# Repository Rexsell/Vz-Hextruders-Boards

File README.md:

This project introduces convenient and useful PCBs designed for the [Vz-Hextrudort-Low](https://github.com/VzBoT3D/Vz-HextrudORT) and [Vz-Hextrudort-Plus](https://aliexpress.com/item/1005006121253410.html?shpMethod=CAINIAO_STANDARD&sku_id=12000036371654824&spm=a2g2w.stores.seller_list.3.317450c0yMkG1R)
Currently, there are no fully suitable toolboards for VzHextruders, as existing options require additional printed parts and are not 100% compatible with the [Vz-Printhead](https://github.com/VzBoT3D/Vz-Printhead-CNC)

# Prerequisites

Before installation, ensure you have a compatible [X-Endstop mount](https://www.printables.com/model/1297201-x-endstop-mount)
Also, use the correct hardware:
- M3x25 screw (for both extruders)
- M3x6 screw (Hextrudort-Low)
- M3x16 screw (Hextrudort-Plus)
- M3 standoffs (Length equal to your motor's height. You may also need a 0.5mm spacer for LDO motors.)
  
# Boards

## [VzHextrudortLow](https://github.com/Rexsell/Vz-Hextrudort-Boards/tree/main/VzHextrudortLow "VzHextrudortLow") and [VzHextrudortPlus](https://github.com/Rexsell/Vz-Hextrudort-Boards/tree/main/VzHextrudortPlus "VzHextrudortPlus")

They are simple commutation boards, they require Molex Microfit 2x10 as an input. Just direct connection, simple yet useful.

## [VzHextrudortPlusCan](https://github.com/Rexsell/Vz-Hextrudort-Boards/tree/main/VzHextrudortPlusCan "VzHextrudortPlusCan") and [VzHextrudortPlusUSB](https://github.com/Rexsell/Vz-Hextrudort-Boards/tree/main/VzHextrudortPlusUSB "VzHextrudortPlusUSB")
These are already CAN and USB boards respectively. USB version has several additional USB connectors for Beacon/Cartographer sensors and other devices. CAN board has only one CAN connector for external devices.

First of all, they are simpled version of toolboards. They were made as two-layer, singlesided PCBs in order to reduce cost and make them assemblable at home.
Secondly, CAN version I ordered and assembled two times, second one I corrected several mistakes. 

Features:
- Onboard NTC sensor
- TMC2209
- Connectors for external probes
- Connector for FilGuard sensor (Supports simple endstop)
- MAX31865 (Only for USB version curently)
- Solder jumper to turn off power LEDs
- RGB LED for motor backlight (Only for USB)
- Molex Microfit 3.0 for heater
- PFET protection from reversed polarity
- 2 Fans connectors

## WARNING!!!

**Before using this project, double-check the hotnd sensor connector schematic. I experienced unstable readings due to this configuration. The cause could be poorly chosen components, suboptimal routing, or a faulty schematic. The issue was completely resolved after connecting the same PT1000 sensor to a MAX31865 board. I used the BTT EBB36 schematic as a reference, but I don't recall exactly how I selected the components — I may have chosen incorrect ones.**

## [VzLowCan-Pro](https://github.com/Rexsell/Vz-Hextrudort-Boards/tree/main/VzLowCan-Pro "VzLowCan-Pro")

It shares the same features (and issues) as the [VzHextrudortPlusUSB](https://github.com/Rexsell/Vz-Hextrudort-Boards/tree/main/VzHextrudortPlusUSB "VzHextrudortPlusUSB"). However, this version is adapted for the -Low model and includes several additional features, such as an extended configuration for the MAX31865 and a connector for a probe like the BL-Touch. It also has a jumper for fan voltage selection. The design is not yet finalized, but I believe more experienced engineers will be able to complete it.

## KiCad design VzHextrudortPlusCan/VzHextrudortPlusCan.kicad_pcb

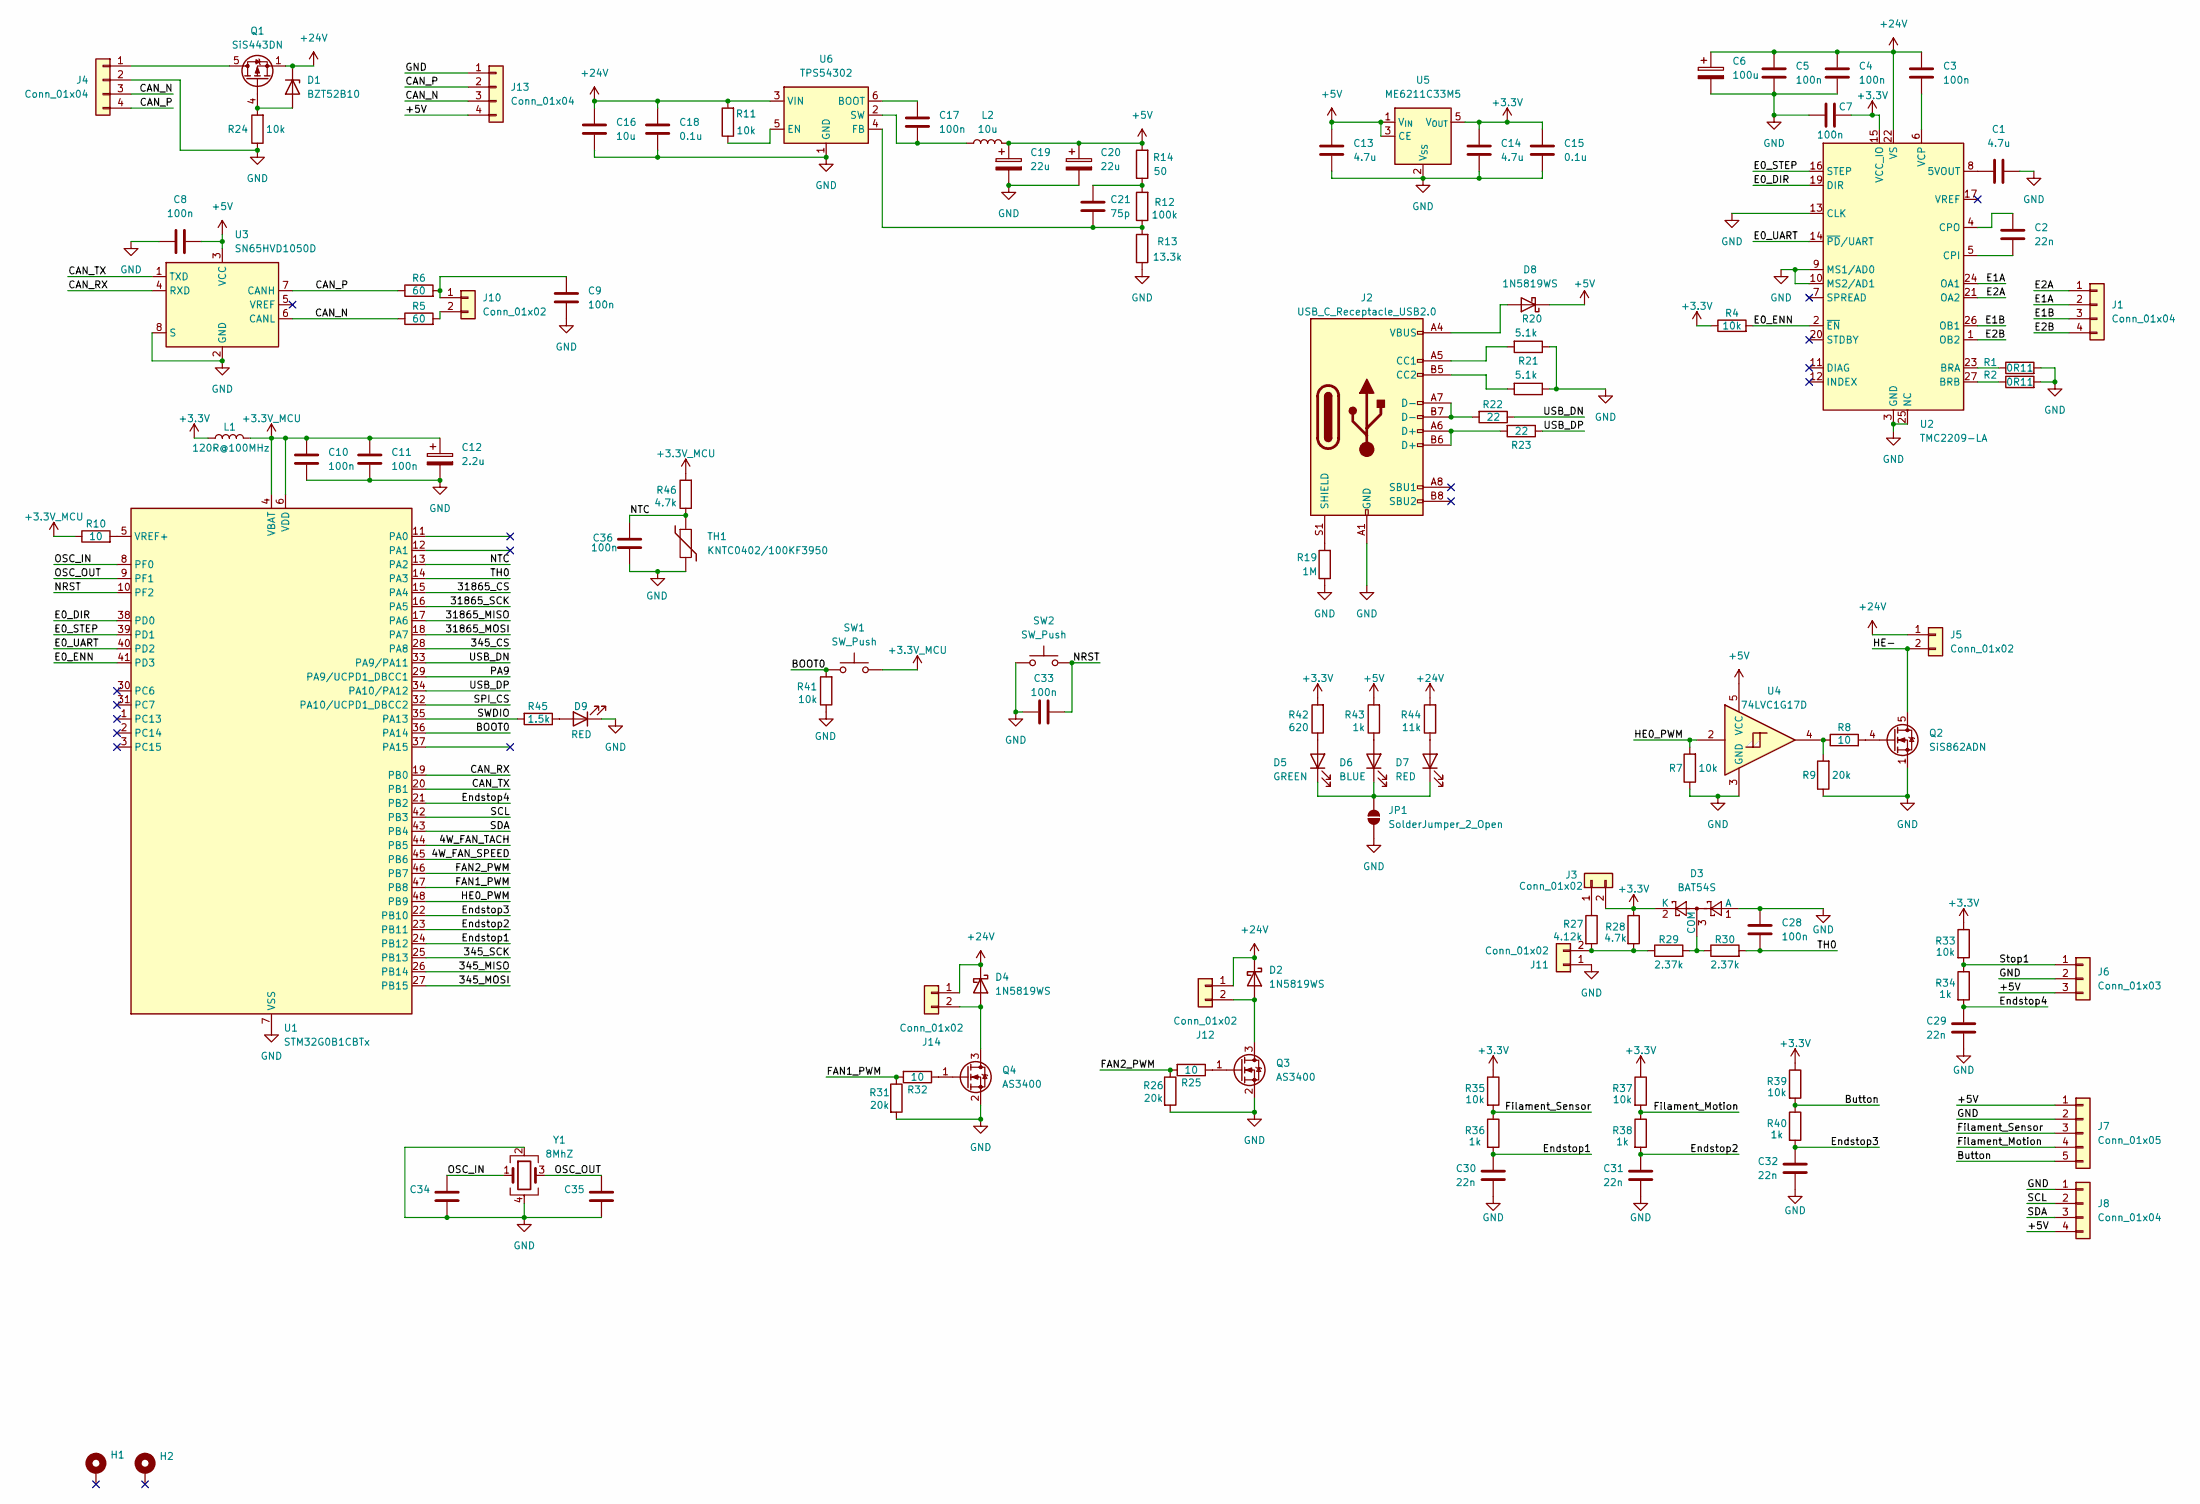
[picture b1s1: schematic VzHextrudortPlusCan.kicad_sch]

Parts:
C1: 4.7u; C_0402_1005Metric
C2, C29, C30, C31, C32, C34, C35: 22n; C_0402_1005Metric
C3, C4, C5, C7, C8, C9, C10, C11, C17, C28, C33, C36: 100n; C_0402_1005Metric
C6: 100u; CP_Elec_6.3x5.2
C12: 2.2u; CP_EIA-2012-12_Kemet-R
C13, C14: 4.7u; C_0603_1608Metric
C15, C18: 0.1u; C_0603_1608Metric
C16: 10u; C_0603_1608Metric
C19, C20: 22u; CP_EIA-3216-18_Kemet-A
C21: 75p; C_0402_1005Metric
D1: BZT52B10; D_SOD-123F
D2, D4, D8: 1N5819WS; D_SOD-323
D3: BAT54S; SOT-23
D5: GREEN; LED_0402_1005Metric
D6: BLUE; LED_0402_1005Metric
D7, D9: RED; LED_0402_1005Metric
H1, H2: MountingHole_Pad; MountingHole_M3
J1: Conn_01x04; JST_XH_B4B-XH-A_1x04_P2.50mm_Vertical
J2: USB_C_Receptacle_USB2.0; USB_C_Receptacle_HRO_TYPE-C-31-M-12
J3, J10: Conn_01x02; PinHeader_1x02_P2.00mm_Vertical
J4: Conn_01x04; XT30PW(2+2)-M.G.B
J5, J11: Conn_01x02; Molex_Micro-Fit_3.0_43045-0200_2x01_P3.00mm_Horizontal
J6: Conn_01x03; JST_PH_B3B-PH-K_1x03_P2.00mm_Vertical
J7: Conn_01x05; JST_PH_B5B-PH-K_1x05_P2.00mm_Vertical
J8, J13: Conn_01x04; JST_PH_B4B-PH-K_1x04_P2.00mm_Vertical
J12, J14: Conn_01x02; JST_PH_B2B-PH-K_1x02_P2.00mm_Vertical
JP1: SolderJumper_2_Open; SolderJumper-2_P1.3mm_Open_TrianglePad1.0x1.5mm
L1: 120R@100MHz; L_0402_1005Metric
L2: 10u; L_APV_APH0530
Q1: SiS443DN; Vishay_PowerPAK_1212-8_Single
Q2: SiS862ADN; Vishay_PowerPAK_1212-8_Single
Q3, Q4: AS3400; SOT-23
R1, R2: 0R11; R_0805_2012Metric
R4, R7, R11, R24, R33, R35, R37, R39: 10k; R_0402_1005Metric
R5, R6: 60; R_0402_1005Metric
R8, R10, R25, R32: 10; R_0402_1005Metric
R9, R26, R31: 20k; R_0402_1005Metric
R12: 100k; R_0402_1005Metric
R13: 13.3k; R_0402_1005Metric
R14: 50; R_0402_1005Metric
R19: 1M; R_0402_1005Metric
R20, R21: 5.1k; R_0402_1005Metric
R22, R23: 22; R_0402_1005Metric
R27: 4.12k; R_0402_1005Metric
R28: 4.7k; R_0402_1005Metric
R29, R30: 2.37k; R_0402_1005Metric
R34, R36, R38, R40: 1k; R_0402_1005Metric
R41: 10k; R_0402_1005Metric; Part Description Resistor 15K M1005 1% 63mW
R42: 620; R_0402_1005Metric; Part Description Resistor 15K M1005 1% 63mW
R43: 1k; R_0402_1005Metric; Part Description Resistor 15K M1005 1% 63mW
R44: 11k; R_0402_1005Metric; Part Description Resistor 15K M1005 1% 63mW
R45: 1.5k; R_0402_1005Metric; Part Description Resistor 15K M1005 1% 63mW
R46: 4.7k; R_0402_1005Metric; Part Description Resistor 15K M1005 1% 63mW
SW1, SW2: SW_Push; SW_Push_1P1T_NO_Vertical_Wuerth_434133025816
TH1: KNTC0402/100KF3950; R_0402_1005Metric
U1: STM32G0B1CBTx; LQFP-48_7x7mm_P0.5mm
U2: TMC2209-LA; VQFN-28-1EP_5x5mm_P0.5mm_EP3.7x3.7mm
U3: SN65HVD1050D; SOIC-8_3.9x4.9mm_P1.27mm
U4: 74LVC1G17D; SOT-23-5
U5: ME6211C33M5; SOT-23-5
U6: TPS54302; SOT-23-6
Y1: 8MhZ; Crystal_SMD_3225-4Pin_3.2x2.5mm

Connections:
+3.3V: C7.1, C14.1, C15.1, D3.2 (K), J3.2, L1.1, R4.1, R28.1, R33.1, R35.1, R37.1, R39.1, R42.2, U2.15 (VCC_IO), U5.5 (V_{OUT})
+3.3V_MCU: C10.2, C11.2, C12.1, L1.2, R10.1, R46.2, SW1.2, U1.4 (VBAT), U1.6 (VDD)
+5V: C8.1, C13.1, C19.1, C20.1, D8.1 (K), J6.3, J7.1, J8.4, J13.4, L2.2, R14.2, R43.2, U3.3 (VCC), U4.5 (VCC), U5.1 (V_{IN}), U5.3 (CE)
+24V: C3.2, C4.2, C5.2, C6.1, C16.1, C18.1, D1.1 (K), D2.1 (K), D4.1 (K), J5.1, J12.1, J14.1, Q1.1 (S), Q1.2 (S), Q1.3 (S), R11.2, R44.2, U2.22 (VS), U2.28 (VS), U6.3 (VIN)
/4W_FAN_SPEED: U1.45 (PB6)
/4W_FAN_TACH: U1.44 (PB5)
/345_CS: U1.28 (PA8)
/345_MISO: U1.26 (PB14)
/345_MOSI: U1.27 (PB15)
/345_SCK: U1.25 (PB13)
/31865_CS: U1.15 (PA4)
/31865_MISO: U1.17 (PA6)
/31865_MOSI: U1.18 (PA7)
/31865_SCK: U1.16 (PA5)
/BOOT0: R41.2, SW1.1, U1.36 (PA14)
/Button: J7.5, R39.2, R40.1
/CAN_N: J4.3, J13.3, R5.1, U3.6 (CANL)
/CAN_P: J4.4, J13.2, R6.1, U3.7 (CANH)
/CAN_RX: U1.19 (PB0), U3.4 (RXD)
/CAN_TX: U1.20 (PB1), U3.1 (TXD)
/E0_DIR: U1.38 (PD0), U2.19 (DIR)
/E0_ENN: R4.2, U1.41 (PD3), U2.2 (~EN)
/E0_STEP: U1.39 (PD1), U2.16 (STEP)
/E0_UART: U1.40 (PD2), U2.14 (~PD/UART)
/E1A: J1.2, U2.24 (OA1)
/E1B: J1.3, U2.26 (OB1)
/E2A: J1.1, U2.21 (OA2)
/E2B: J1.4, U2.1 (OB2)
/Endstop1: C30.1, R36.2, U1.24 (PB12)
/Endstop2: C31.1, R38.2, U1.23 (PB11)
/Endstop3: C32.1, R40.2, U1.22 (PB10)
/Endstop4: C29.1, R34.2, U1.21 (PB2)
/FAN1_PWM: R31.1, R32.2, U1.47 (PB8)
/FAN2_PWM: R25.2, R26.1, U1.46 (PB7)
/Filament_Motion: J7.4, R37.2, R38.1
/Filament_Sensor: J7.3, R35.2, R36.1
/HE0_PWM: R7.2, U1.48 (PB9), U4.2
/HE-: J5.2, Q2.5 (D)
/NRST: C33.1, SW2.2, U1.10 (PF2)
/NTC: C36.1, R46.1, TH1.1, U1.13 (PA2)
/OSC_IN: C34.1, U1.8 (PF0), Y1.1
/OSC_OUT: C35.1, U1.9 (PF1), Y1.3
/PA9: U1.29 (PA9/UCPD1_DBCC1)
/SCL: J8.2, U1.42 (PB3)
/SDA: J8.3, U1.43 (PB4)
/SPI_CS: U1.32 (PA10/UCPD1_DBCC2)
/SWDIO: R45.2, U1.35 (PA13)
/Stop1: J6.1, R33.2, R34.1
/TH0: C28.1, R30.2, U1.14 (PA3)
/USB_DN: R22.1, U1.33 (PA9/PA11)
/USB_DP: R23.1, U1.34 (PA10/PA12)
GND: C1.2, C4.1, C5.1, C6.2, C7.2, C8.2, C9.1, C10.1, C11.1, C12.2, C13.2, C14.2, C15.2, C16.2, C18.2, C19.2, C20.2, C28.2, C29.2, C30.2, C31.2, C32.2, C33.2, C34.2, C35.2, C36.2, D3.1 (A), D9.1 (K), J2.A1 (GND), J2.A12 (GND), J2.B1 (GND), J2.B12 (GND), J4.2, J6.2, J7.2, J8.1, J11.1, J13.1, JP1.1 (A), Q2.1 (S), Q2.2 (S), Q2.3 (S), Q3.2 (S), Q4.2 (S), R1.2, R2.2, R7.1, R9.1, R13.1, R19.1, R20.1, R21.1, R24.1, R26.2, R31.2, R41.1, SW2.1, TH1.2, U1.7 (VSS), U2.3 (GND), U2.9 (MS1/AD0), U2.10 (MS2/AD1), U2.13 (CLK), U2.18 (GND), U2.25 (NC), U2.29 (GND), U3.2 (GND), U3.8 (S), U4.3 (GND), U5.2 (V_{SS}), U6.1 (GND), Y1.2, Y1.4
unnamed: C21.2, R12.2, R14.1
unnamed: D1.2 (A), Q1.4 (G), R24.2
unnamed: D2.2 (A), J12.2, Q3.3 (D)
unnamed: D3.3 (COM), R29.2, R30.1
unnamed: D4.2 (A), J14.2, Q4.3 (D)
unnamed: D5.2 (A), R42.1
unnamed: D5.1 (K), D6.1 (K), D7.1 (K), JP1.2 (B)
unnamed: D6.2 (A), R43.1
unnamed: D7.2 (A), R44.1
unnamed: D8.2 (A), J2.A4 (VBUS), J2.A9 (VBUS), J2.B4 (VBUS), J2.B9 (VBUS)
unnamed: D9.2 (A), R45.1
unnamed: J2.A5 (CC1), R20.2
unnamed: J2.B5 (CC2), R21.2
unnamed: J2.A6 (D+), J2.B6 (D+), R23.2
unnamed: J2.A7 (D-), J2.B7 (D-), R22.2
unnamed: J2.S1 (SHIELD), R19.2
unnamed: J3.1, R27.1
unnamed: J4.1, Q1.5 (D)
unnamed: C9.2, J10.1, R6.2
unnamed: J10.2, R5.2
unnamed: J11.2, R27.2, R28.2, R29.1
unnamed: Q2.4 (G), R8.2
unnamed: Q3.1 (G), R25.1
unnamed: Q4.1 (G), R32.1
unnamed: R8.1, R9.2, U4.4
unnamed: R10.2, U1.5 (VREF+)
unnamed: C1.1, U2.8 (5VOUT)
unnamed: R1.1, U2.23 (BRA)
unnamed: R2.1, U2.27 (BRB)
unnamed: C2.1, U2.5 (CPI)
unnamed: C2.2, U2.4 (CPO)
unnamed: C3.1, U2.6 (VCP)
unnamed: C17.2, U6.6 (BOOT)
unnamed: R11.1, U6.5 (EN)
unnamed: C21.1, R12.1, R13.2, U6.4 (FB)
unnamed: C17.1, L2.1, U6.2 (SW)

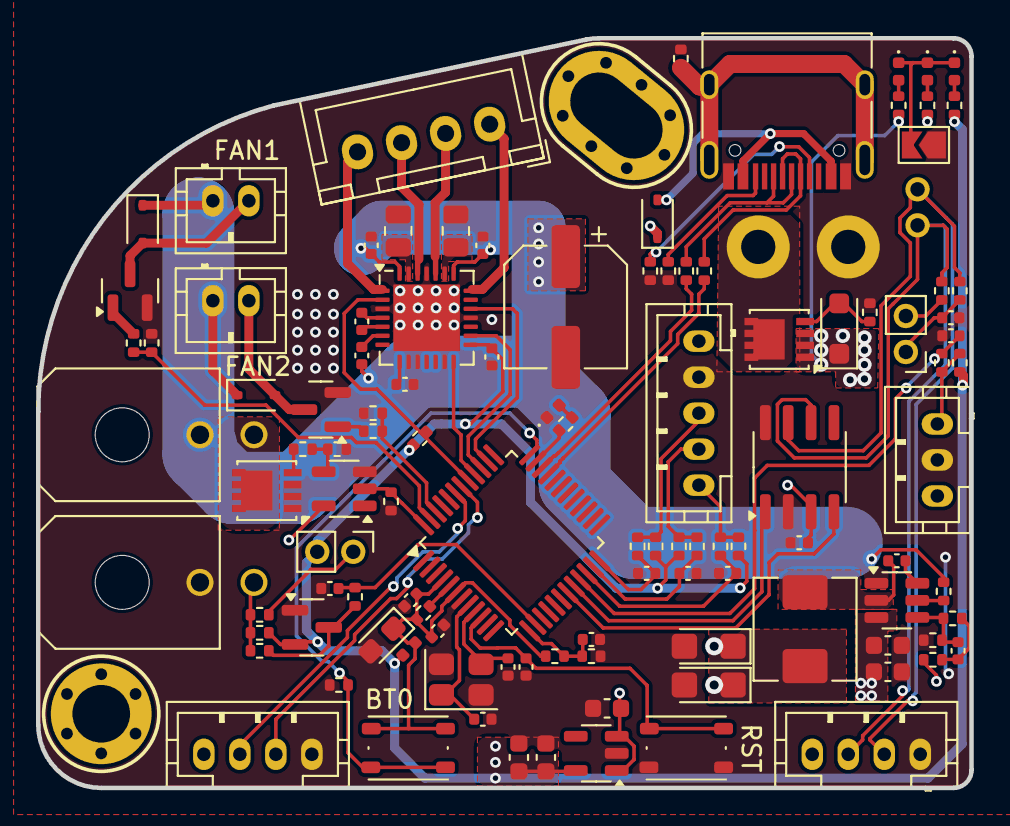
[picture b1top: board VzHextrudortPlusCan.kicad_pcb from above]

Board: 2 copper layers, 51.8 x 41.6 mm, 112 parts (1 on the bottom side), 76 nets.

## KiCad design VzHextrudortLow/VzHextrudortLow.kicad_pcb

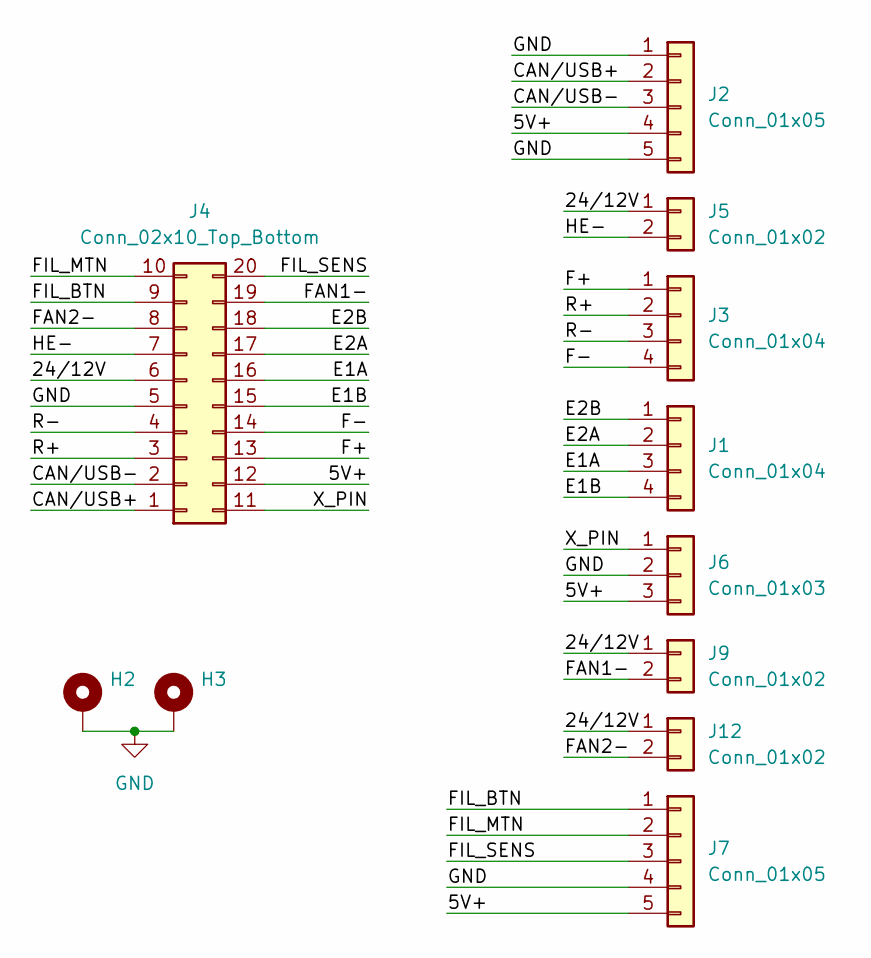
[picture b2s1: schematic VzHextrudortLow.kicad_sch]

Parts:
H2, H3: MountingHole_Pad; MountingHole_M3
J1: Conn_01x04; JST_XH_S4B-XH-A_1x04_P2.50mm_Horizontal
J2, J7: Conn_01x05; JST_PH_B5B-PH-K_1x05_P2.00mm_Vertical
J3: Conn_01x04; JST_PH_B4B-PH-K_1x04_P2.00mm_Vertical
J4: Conn_02x10_Top_Bottom; Molex_Micro-Fit_3.0_43045-2012_2x10_P3.00mm_Vertical
J5: Conn_01x02; Molex_Micro-Fit_3.0_43045-0200_2x01_P3.00mm_Horizontal
J6: Conn_01x03; JST_PH_B3B-PH-K_1x03_P2.00mm_Vertical
J9, J12: Conn_01x02; JST_PH_B2B-PH-K_1x02_P2.00mm_Vertical

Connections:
/5V+: J2.4, J4.12, J6.3, J7.5
/24/12V: J4.6, J5.1, J9.1, J12.1
/CAN/USB+: J2.2, J4.1
/CAN/USB-: J2.3, J4.2
/E1A: J1.3, J4.16
/E1B: J1.4, J4.15
/E2A: J1.2, J4.17
/E2B: J1.1, J4.18
/F+: J3.1, J4.13
/F-: J3.4, J4.14
/FAN1-: J4.19, J9.2
/FAN2-: J4.8, J12.2
/FIL_BTN: J4.9, J7.1
/FIL_MTN: J4.10, J7.2
/FIL_SENS: J4.20, J7.3
/HE-: J4.7, J5.2
/R+: J3.2, J4.3
/R-: J3.3, J4.4
/X_PIN: J4.11, J6.1
GND: H2.1, H3.1, J2.1, J2.5, J4.5, J6.2, J7.4

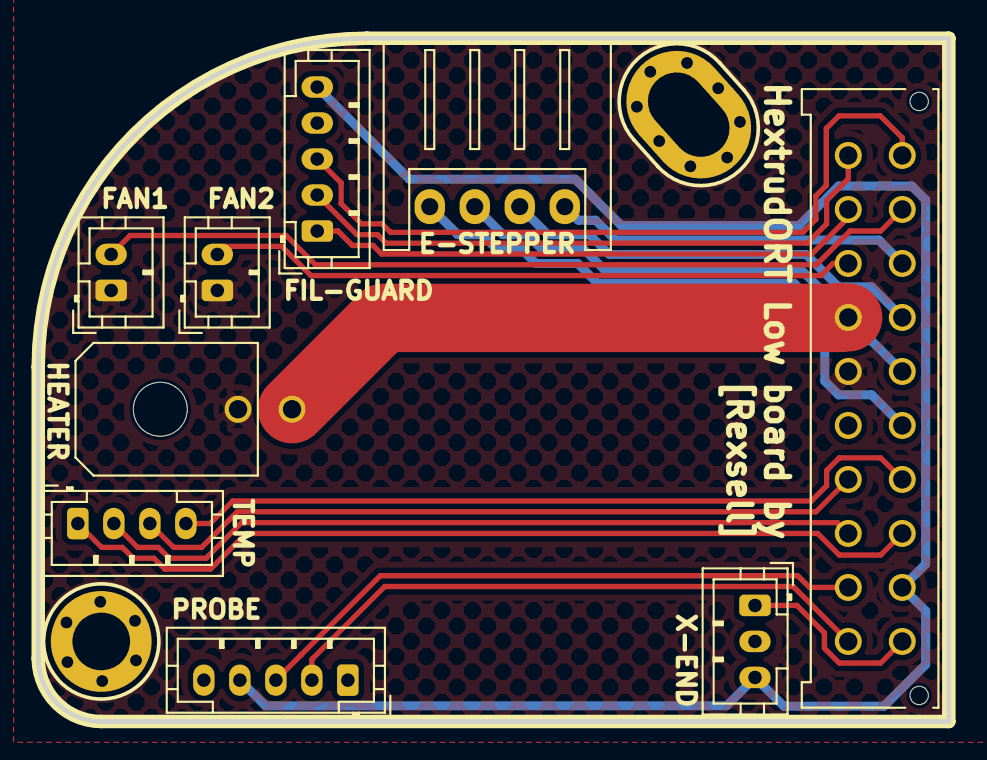
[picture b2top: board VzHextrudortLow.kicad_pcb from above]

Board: 2 copper layers, 50.6 x 38.0 mm, 11 parts (0 on the bottom side), 20 nets.

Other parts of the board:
H1: MountingHole_Pad; MountingHole_M3

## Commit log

2026-02-08 Rename Vz-Hextrudort-Boards.md to README.md
